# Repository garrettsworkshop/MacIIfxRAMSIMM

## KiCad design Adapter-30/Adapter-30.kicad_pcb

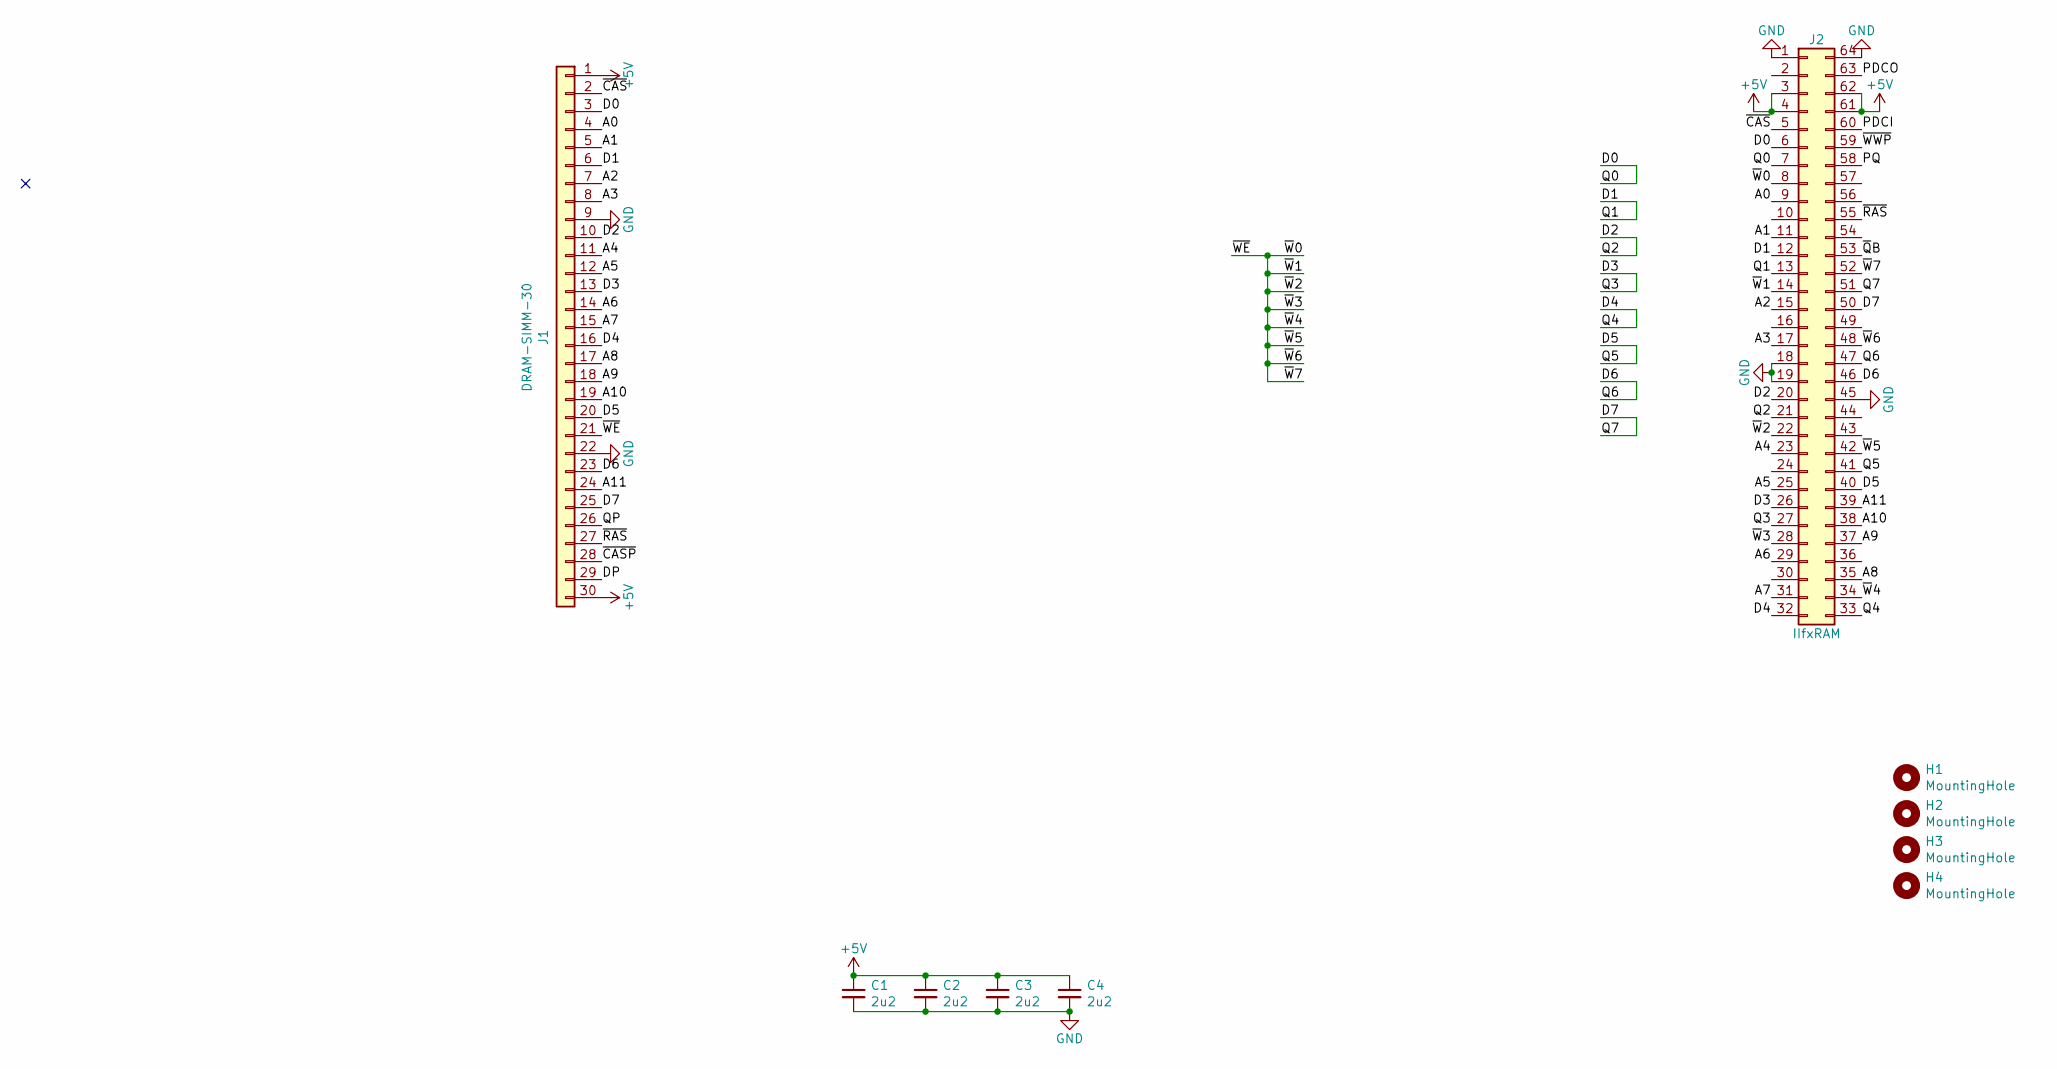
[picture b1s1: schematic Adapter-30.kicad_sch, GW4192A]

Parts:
C1, C2, C3, C4: 2u2; C_0805
H1, H2, H3, H4: MountingHole; PasteHole_1.152mm_NPTH
J1: DRAM-SIMM-30; SIMM-30_Edge
J2: IIfxRAM; SIMM-64_Socket_TH_P1.27mm

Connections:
+5V: C1.1, C2.1, C3.1, C4.1, J1.1, J1.30, J2.3, J2.4, J2.61, J2.62
/A0: J1.4, J2.9
/A1: J1.5, J2.11
/A2: J1.7, J2.15
/A3: J1.8, J2.17
/A4: J1.11, J2.23
/A5: J1.12, J2.25
/A6: J1.14, J2.29
/A7: J1.15, J2.31
/A8: J1.17, J2.35
/A9: J1.18, J2.37
/A10: J1.19, J2.38
/A11: J1.24, J2.39
/D0: J1.3, J2.6, J2.7
/D1: J1.6, J2.12, J2.13
/D2: J1.10, J2.20, J2.21
/D3: J1.13, J2.26, J2.27
/D4: J1.16, J2.32, J2.33
/D5: J1.20, J2.40, J2.41
/D6: J1.23, J2.46, J2.47
/D7: J1.25, J2.50, J2.51
/DP: J1.29
/PDCI: J2.60
/PDCO: J2.63
/PQ: J2.58
/QP: J1.26
/~CASP: J1.28
/~CAS: J1.2, J2.5
/~QB: J2.53
/~RAS: J1.27, J2.55
/~WE: J1.21, J2.8, J2.14, J2.22, J2.28, J2.34, J2.42, J2.48, J2.52
/~WWP: J2.59
GND: C1.2, C2.2, C3.2, C4.2, J1.9, J1.22, J2.1, J2.18, J2.19, J2.45, J2.64

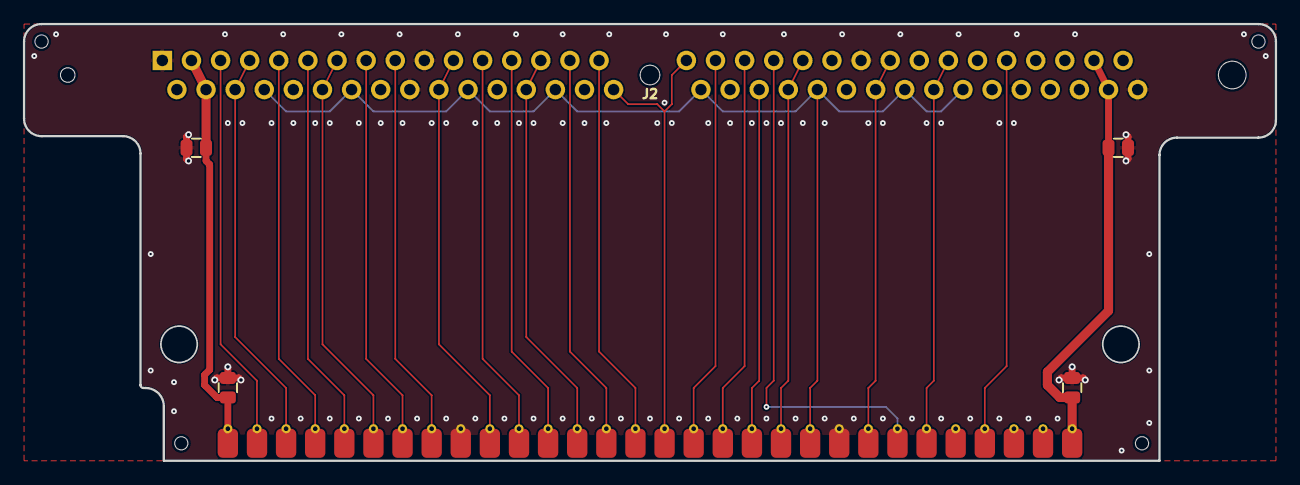
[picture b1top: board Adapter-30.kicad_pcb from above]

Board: 2 copper layers, 109.2 x 38.1 mm, 10 parts (0 on the bottom side), 25 nets.

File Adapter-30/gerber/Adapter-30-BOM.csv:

"Ref","Qnty","Value","Cmp name","Footprint","Description","Vendor","LCSC Part"
"C1, C2, C3, C4, ","4","2u2","C_Small","stdpads:C_0805","Unpolarized capacitor, small symbol","",""
"H1, H2, H3, H4, ","4","MountingHole","MountingHole","stdpads:PasteHole_1.152mm_NPTH","Mounting Hole without connection","",""
"J1, ","1","DRAM-SIMM-30","Conn_01x30","stdpads:SIMM-30_Edge","Generic connector, single row, 01x30, script generated (kicad-library-utils/schlib/autogen/connector/)","",""
"J2, ","1","IIfxRAM","Conn_02x32_Counter_Clockwise","stdpads:SIMM-64_Socket_TH_P1.27mm","Generic connector, double row, 02x32, counter clockwise pin numbering scheme (similar to DIP packge numbering), script generated (kicad-library-utils/schlib/autogen/connector/)","",""

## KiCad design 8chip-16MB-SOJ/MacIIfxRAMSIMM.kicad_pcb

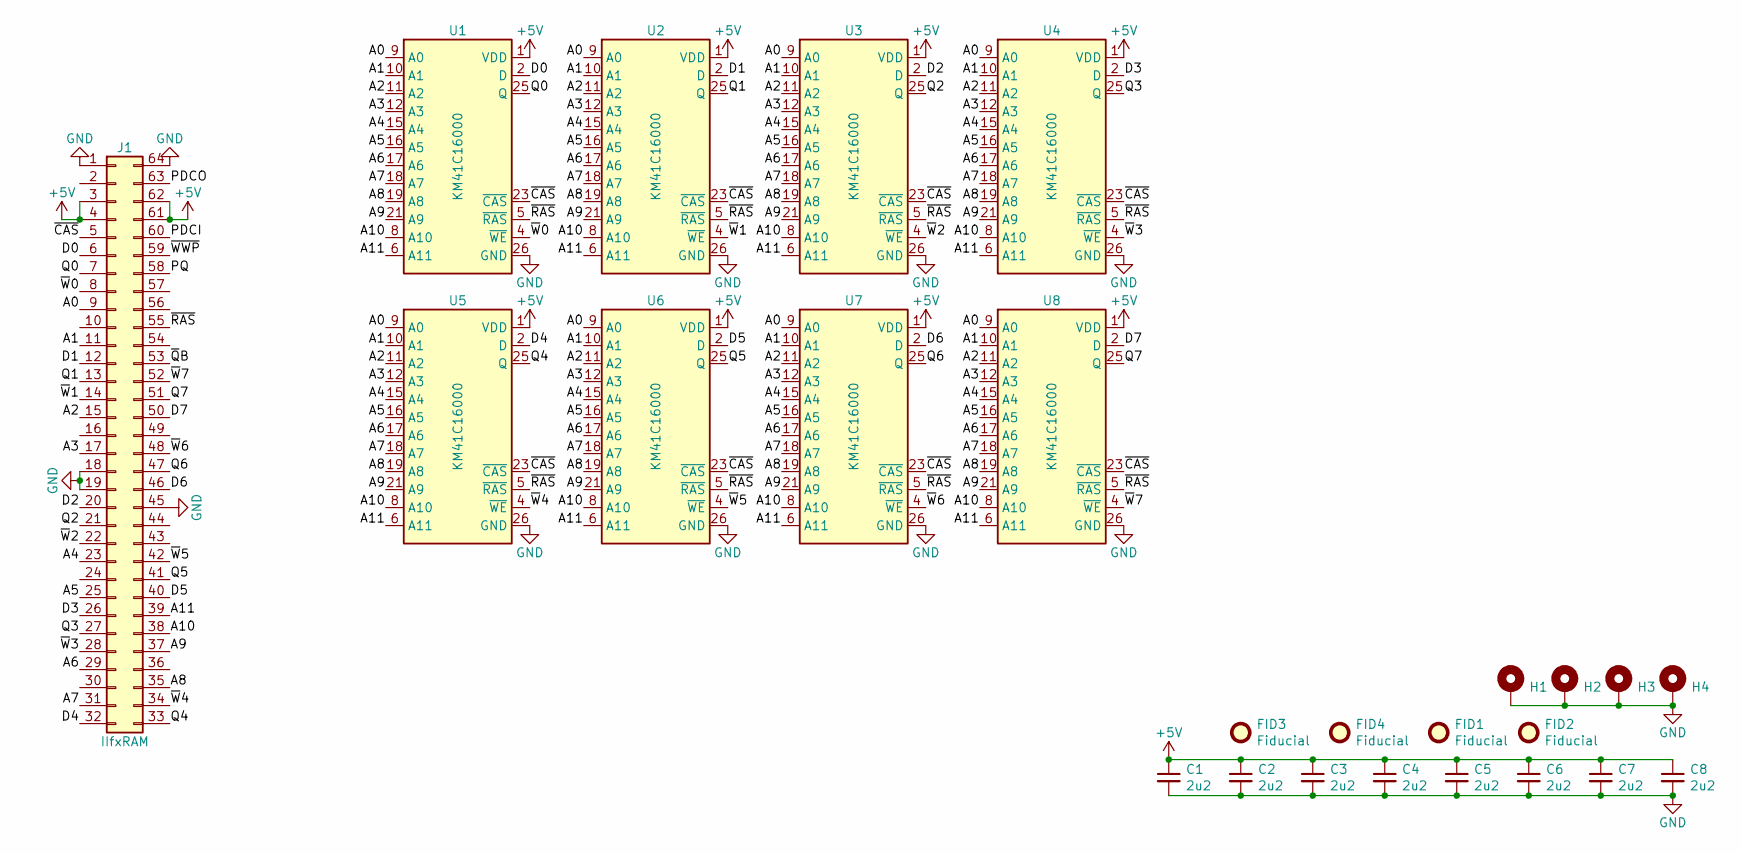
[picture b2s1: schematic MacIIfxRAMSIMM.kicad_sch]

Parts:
C1, C2, C3, C4, C5, C6, C7, C8: 2u2; C_0805
FID1, FID2, FID3, FID4: Fiducial
H1, H2, H3, H4: PasteHole_1.1mm_PTH
J1: IIfxRAM; MacIIROMSIMM_Edge
U1, U2, U3, U4, U5, U6, U7, U8: KM41C16000; SOP-24-26-300mil

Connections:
+5V: C1.1, C2.1, C3.1, C4.1, C5.1, C6.1, C7.1, C8.1, J1.3, J1.4, J1.61, J1.62, U1.1 (VDD), U1.13 (VDD), U2.1 (VDD), U2.13 (VDD), U3.1 (VDD), U3.13 (VDD), U4.1 (VDD), U4.13 (VDD), U5.1 (VDD), U5.13 (VDD), U6.1 (VDD), U6.13 (VDD), U7.1 (VDD), U7.13 (VDD), U8.1 (VDD), U8.13 (VDD); also elsewhere on the board
/A0: J1.9, U1.9 (A0), U2.9 (A0), U3.9 (A0), U4.9 (A0), U5.9 (A0), U6.9 (A0), U7.9 (A0), U8.9 (A0)
/A1: J1.11, U1.10 (A1), U2.10 (A1), U3.10 (A1), U4.10 (A1), U5.10 (A1), U6.10 (A1), U7.10 (A1), U8.10 (A1)
/A2: J1.15, U1.11 (A2), U2.11 (A2), U3.11 (A2), U4.11 (A2), U5.11 (A2), U6.11 (A2), U7.11 (A2), U8.11 (A2)
/A3: J1.17, U1.12 (A3), U2.12 (A3), U3.12 (A3), U4.12 (A3), U5.12 (A3), U6.12 (A3), U7.12 (A3), U8.12 (A3)
/A4: J1.23, U1.15 (A4), U2.15 (A4), U3.15 (A4), U4.15 (A4), U5.15 (A4), U6.15 (A4), U7.15 (A4), U8.15 (A4)
/A5: J1.25, U1.16 (A5), U2.16 (A5), U3.16 (A5), U4.16 (A5), U5.16 (A5), U6.16 (A5), U7.16 (A5), U8.16 (A5)
/A6: J1.29, U1.17 (A6), U2.17 (A6), U3.17 (A6), U4.17 (A6), U5.17 (A6), U6.17 (A6), U7.17 (A6), U8.17 (A6)
/A7: J1.31, U1.18 (A7), U2.18 (A7), U3.18 (A7), U4.18 (A7), U5.18 (A7), U6.18 (A7), U7.18 (A7), U8.18 (A7)
/A8: J1.35, U1.19 (A8), U2.19 (A8), U3.19 (A8), U4.19 (A8), U5.19 (A8), U6.19 (A8), U7.19 (A8), U8.19 (A8)
/A9: J1.37, U1.21 (A9), U2.21 (A9), U3.21 (A9), U4.21 (A9), U5.21 (A9), U6.21 (A9), U7.21 (A9), U8.21 (A9)
/A10: J1.38, U1.8 (A10), U2.8 (A10), U3.8 (A10), U4.8 (A10), U5.8 (A10), U6.8 (A10), U7.8 (A10), U8.8 (A10)
/A11: J1.39, U1.6 (A11), U2.6 (A11), U3.6 (A11), U4.6 (A11), U5.6 (A11), U6.6 (A11), U7.6 (A11), U8.6 (A11)
/D0: J1.6, U1.2 (D)
/D1: J1.12, U2.2 (D)
/D2: J1.20, U3.2 (D)
/D3: J1.26, U4.2 (D)
/D4: J1.32, U5.2 (D)
/D5: J1.40, U6.2 (D)
/D6: J1.46, U7.2 (D)
/D7: J1.50, U8.2 (D)
/PDCI: J1.60
/PDCO: J1.63
/PQ: J1.58
/Q0: J1.7, U1.25 (Q)
/Q1: J1.13, U2.25 (Q)
/Q2: J1.21, U3.25 (Q)
/Q3: J1.27, U4.25 (Q)
/Q4: J1.33, U5.25 (Q)
/Q5: J1.41, U6.25 (Q)
/Q6: J1.47, U7.25 (Q)
/Q7: J1.51, U8.25 (Q)
/~CAS: J1.5, U1.23 (~CAS), U2.23 (~CAS), U3.23 (~CAS), U4.23 (~CAS), U5.23 (~CAS), U6.23 (~CAS), U7.23 (~CAS), U8.23 (~CAS)
/~QB: J1.53
/~RAS: J1.55, U1.5 (~RAS), U2.5 (~RAS), U3.5 (~RAS), U4.5 (~RAS), U5.5 (~RAS), U6.5 (~RAS), U7.5 (~RAS), U8.5 (~RAS)
/~WWP: J1.59
/~W0: J1.8, U1.4 (~WE)
/~W1: J1.14, U2.4 (~WE)
/~W2: J1.22, U3.4 (~WE)
/~W3: J1.28, U4.4 (~WE)
/~W4: J1.34, U5.4 (~WE)
/~W5: J1.42, U6.4 (~WE)
/~W6: J1.48, U7.4 (~WE)
/~W7: J1.52, U8.4 (~WE)
GND: C1.2, C2.2, C3.2, C4.2, C5.2, C6.2, C7.2, C8.2, H1.1, H2.1, H3.1, H4.1, J1.1, J1.18, J1.19, J1.45, J1.64, U1.14 (GND), U1.26 (GND), U2.14 (GND), U2.26 (GND), U3.14 (GND), U3.26 (GND), U4.14 (GND), U4.26 (GND), U5.14 (GND), U5.26 (GND), U6.14 (GND), U6.26 (GND), U7.14 (GND), U7.26 (GND), U8.14 (GND), U8.26 (GND); also elsewhere on the board

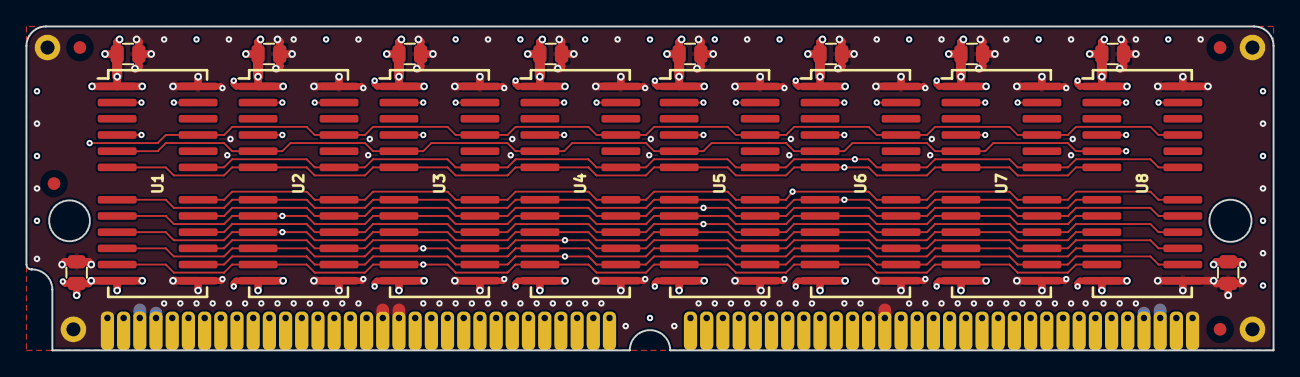
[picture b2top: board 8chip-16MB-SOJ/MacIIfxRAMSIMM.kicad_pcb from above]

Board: 4 copper layers, 97.8 x 25.4 mm, 27 parts (0 on the bottom side), 40 nets.

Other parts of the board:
C8#2, C8#3: 2u2; C_0805

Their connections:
+5V: C8#2.1, C8#3.1; also elsewhere on the board
GND: C8#2.2, C8#3.2; also elsewhere on the board

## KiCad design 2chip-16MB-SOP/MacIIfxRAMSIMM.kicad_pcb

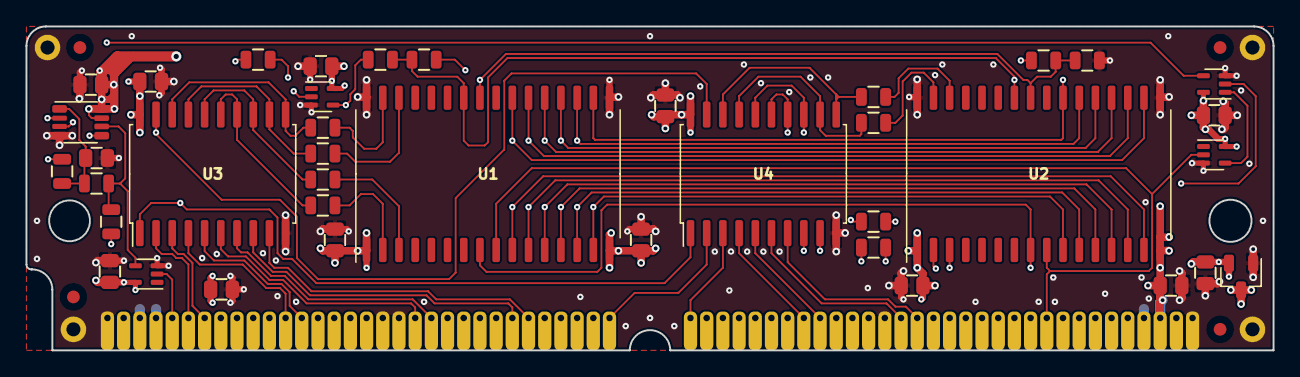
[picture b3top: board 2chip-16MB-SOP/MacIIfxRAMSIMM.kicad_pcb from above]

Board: 4 copper layers, 97.8 x 25.4 mm, 48 parts (0 on the bottom side), 60 nets.

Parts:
C1, C2, C3, C4, C5, C6, C7, C8, C9, C10, C11, C12: 2u2; C_0805
C13: 22p; C_0805
FID1, FID2, FID3, FID4: Fiducial
H1, H2, H3, H4: PasteHole_1.1mm_PTH
J1: IIfxRAM; MacIIROMSIMM_Edge
R1, R2, R3, R4, R5, R6, R7, R8, R9: 100; R_0805
R10: EDO0; R_0805
R11: EDO1; R_0805
R12: FPM; R_0805
R13: CASd; R_0805
R14: CAS; R_0805
R15: RCAS; R_0805
R16: RCASd; R_0805
U1, U2: KM44C16104; SOP-32_400mil
U3, U4: 74AHCT244PW; SOIC-20W_7.5mm
U5, U6, U9: 74LVC1G04GW; SOT-353
U7: 74LVC1G08GW; SOT-353
U8: 74LVC1G74DC; NXP_TSSOP-8_3x3mm_P0.65mm
U10: XC6206PxxxMR; SOT-23

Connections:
+3V3: C8.1, C9.1, C10.1, C11.1, C12.1, U5.5, U6.5, U7.5, U8.7, U8.8, U9.5, U10.2
+5V: C1.1, C2.1, C3.1, C4.1, C5.1, C6.1, C7.1, J1.3, J1.4, J1.61, J1.62, U1.1, U1.16, U2.1, U2.16, U3.20, U4.20, U10.3
/A0: J1.9, U1.10, U2.15
/A1: J1.11, U1.11, U2.14
/A2: J1.15, U1.12, U2.13
/A3: J1.17, U1.13, U2.12
/A4: J1.23, U1.14, U2.11
/A5: J1.25, U1.15, U2.10
/A6: J1.29, U1.23, U2.18
/A7: J1.31, U1.22, U2.19
/A8: J1.35, U1.21, U2.20
/A9: J1.37, U1.20, U2.21
/A10: J1.38, U1.19, U2.22
/A11: J1.39, U1.18, U2.23
/CAS: R1.2, R14.2, U6.4, U8.6
/CASd: C13.1, R1.1, R13.2, U8.1
/D0: J1.6, U3.2
/D1: J1.12, U3.4
/D2: J1.20, U3.6
/D3: J1.26, U3.8
/D4: J1.32, U4.2
/D5: J1.40, U4.4
/D6: J1.46, U4.6
/D7: J1.50, U4.8
/DQ0: R6.1, U3.12, U3.17
/DQ1: R2.1, U3.14, U3.15
/DQ2: R4.1, U3.13, U3.16
/DQ3: R8.1, U3.11, U3.18
/DQ4: R9.1, U4.12, U4.17
/DQ5: R5.1, U4.14, U4.15
/DQ6: R3.1, U4.13, U4.16
/DQ7: R7.1, U4.11, U4.18
/DQr0: R6.2, U1.30
/DQr1: R2.2, U1.2
/DQr2: R4.2, U1.3
/DQr3: R8.2, U1.31
/DQr4: R9.2, U2.31
/DQr5: R5.2, U2.3
/DQr6: R3.2, U2.2
/DQr7: R7.2, U2.30
/Din~OE~: U3.1, U4.1, U8.5
/Dout~OE~: U3.19, U4.19, U8.3
/Q0: J1.7, U3.3
/Q1: J1.13, U3.5
/Q2: J1.21, U3.7
/Q3: J1.27, U3.9
/Q4: J1.33, U4.3
/Q5: J1.41, U4.5
/Q6: J1.47, U4.7
/Q7: J1.51, U4.9
/RAS: U5.4, U7.1
/RD: U7.4, U8.2
/R~CAS~: R15.2, R16.2, U1.26, U2.26
/~CAS~: J1.5, R10.1, R15.1, U6.2
/~CAS~d: R11.1, R16.1, U9.4
/~OE~: R10.2, R11.2, R12.1, U1.25, U2.25
/~RAS~: J1.55, U1.9, U2.9, U5.2
/~WE~: U1.8, U2.8, U7.2
GND: C1.2, C2.2, C3.2, C4.2, C5.2, C6.2, C7.2, C8.2, C9.2, C10.2, C11.2, C12.2, C13.2, H1.1, H2.1, H3.1, H4.1, J1.1, J1.18, J1.19, J1.45, J1.64, R12.2, U1.17, U1.32, U2.17, U2.32, U3.10, U4.10, U5.3, U6.3, U7.3, U8.4, U9.3, U10.1
unnamed: R13.1, R14.1, U9.2

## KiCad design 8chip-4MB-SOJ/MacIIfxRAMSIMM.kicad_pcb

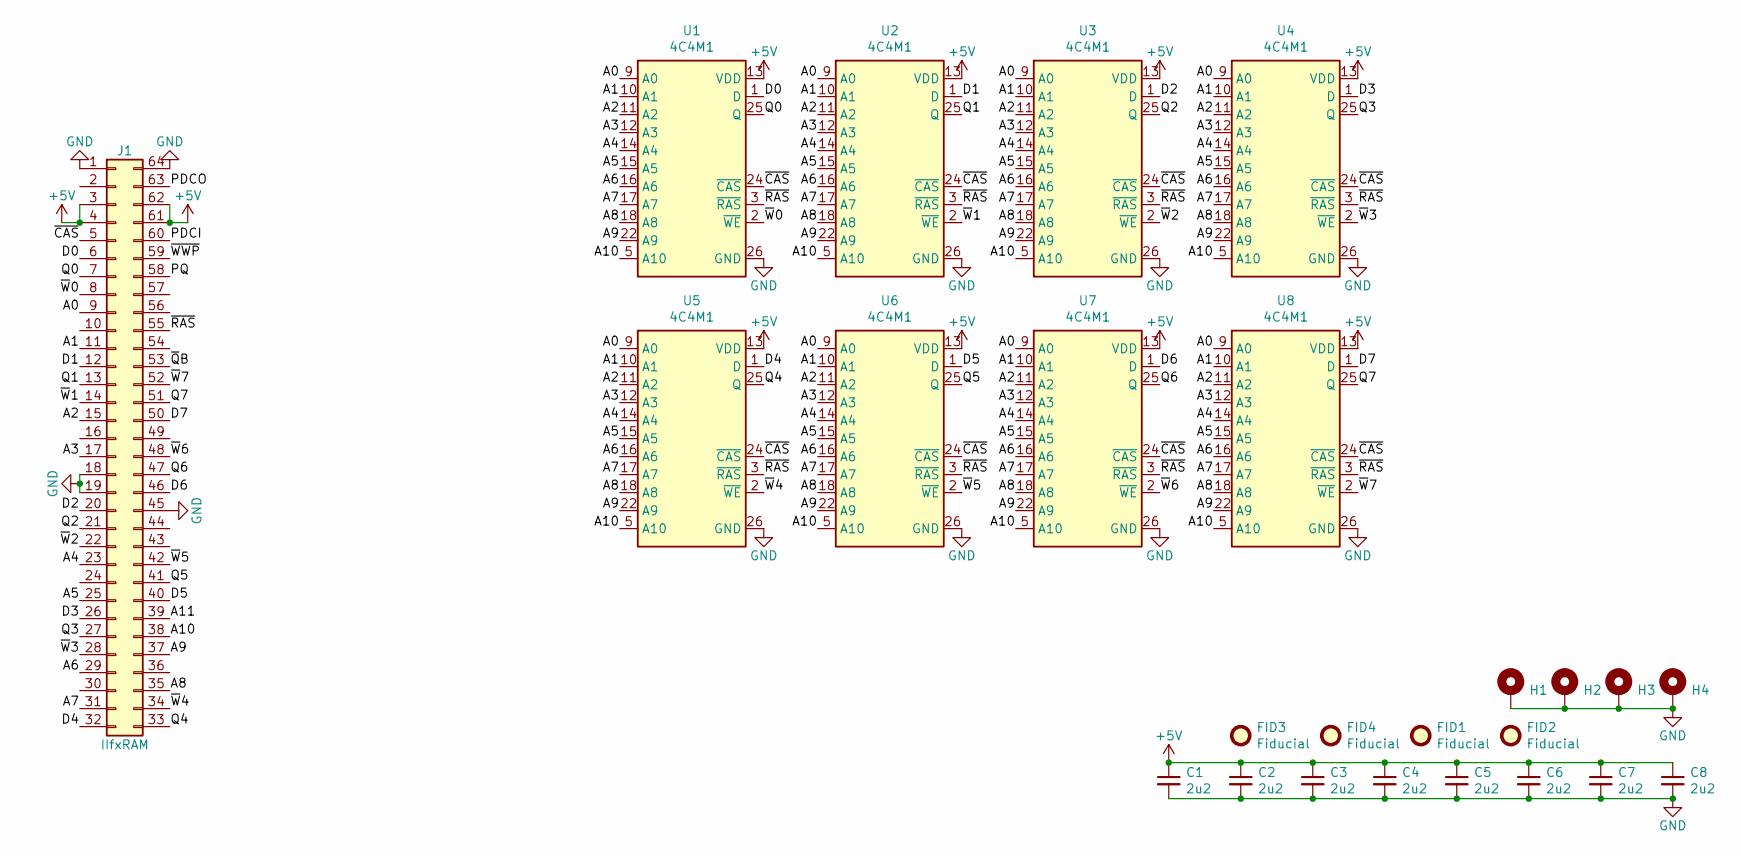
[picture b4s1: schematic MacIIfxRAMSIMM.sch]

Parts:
C1, C2, C3, C4, C5, C6, C7, C8: 2u2; C_0805
FID1, FID2, FID3, FID4: Fiducial
H1, H2, H3, H4: PasteHole_1.1mm_PTH
J1: IIfxRAM; MacIIROMSIMM_Edge
U1, U2, U3, U4, U5, U6, U7, U8: 4C4M1; SOJ-20-26_300mil

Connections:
+5V: C1.1, C2.1, C3.1, C4.1, C5.1, C6.1, C7.1, C8.1, J1.3, J1.4, J1.61, J1.62, U1.13 (VDD), U2.13 (VDD), U3.13 (VDD), U4.13 (VDD), U5.13 (VDD), U6.13 (VDD), U7.13 (VDD), U8.13 (VDD)
/A0: J1.9, U1.9 (A0), U2.9 (A0), U3.9 (A0), U4.9 (A0), U5.9 (A0), U6.9 (A0), U7.9 (A0), U8.9 (A0)
/A1: J1.11, U1.10 (A1), U2.10 (A1), U3.10 (A1), U4.10 (A1), U5.10 (A1), U6.10 (A1), U7.10 (A1), U8.10 (A1)
/A2: J1.15, U1.11 (A2), U2.11 (A2), U3.11 (A2), U4.11 (A2), U5.11 (A2), U6.11 (A2), U7.11 (A2), U8.11 (A2)
/A3: J1.17, U1.12 (A3), U2.12 (A3), U3.12 (A3), U4.12 (A3), U5.12 (A3), U6.12 (A3), U7.12 (A3), U8.12 (A3)
/A4: J1.23, U1.14 (A4), U2.14 (A4), U3.14 (A4), U4.14 (A4), U5.14 (A4), U6.14 (A4), U7.14 (A4), U8.14 (A4)
/A5: J1.25, U1.15 (A5), U2.15 (A5), U3.15 (A5), U4.15 (A5), U5.15 (A5), U6.15 (A5), U7.15 (A5), U8.15 (A5)
/A6: J1.29, U1.16 (A6), U2.16 (A6), U3.16 (A6), U4.16 (A6), U5.16 (A6), U6.16 (A6), U7.16 (A6), U8.16 (A6)
/A7: J1.31, U1.17 (A7), U2.17 (A7), U3.17 (A7), U4.17 (A7), U5.17 (A7), U6.17 (A7), U7.17 (A7), U8.17 (A7)
/A8: J1.35, U1.18 (A8), U2.18 (A8), U3.18 (A8), U4.18 (A8), U5.18 (A8), U6.18 (A8), U7.18 (A8), U8.18 (A8)
/A9: J1.37, U1.22 (A9), U2.22 (A9), U3.22 (A9), U4.22 (A9), U5.22 (A9), U6.22 (A9), U7.22 (A9), U8.22 (A9)
/A10: J1.38, U1.5 (A10), U2.5 (A10), U3.5 (A10), U4.5 (A10), U5.5 (A10), U6.5 (A10), U7.5 (A10), U8.5 (A10)
/A11: J1.39
/D0: J1.6, U1.1 (D)
/D1: J1.12, U2.1 (D)
/D2: J1.20, U3.1 (D)
/D3: J1.26, U4.1 (D)
/D4: J1.32, U5.1 (D)
/D5: J1.40, U6.1 (D)
/D6: J1.46, U7.1 (D)
/D7: J1.50, U8.1 (D)
/PDCI: J1.60
/PDCO: J1.63
/PQ: J1.58
/Q0: J1.7, U1.25 (Q)
/Q1: J1.13, U2.25 (Q)
/Q2: J1.21, U3.25 (Q)
/Q3: J1.27, U4.25 (Q)
/Q4: J1.33, U5.25 (Q)
/Q5: J1.41, U6.25 (Q)
/Q6: J1.47, U7.25 (Q)
/Q7: J1.51, U8.25 (Q)
/~CAS~: J1.5, U1.24 (~CAS~), U2.24 (~CAS~), U3.24 (~CAS~), U4.24 (~CAS~), U5.24 (~CAS~), U6.24 (~CAS~), U7.24 (~CAS~), U8.24 (~CAS~)
/~Q~B: J1.53
/~RAS~: J1.55, U1.3 (~RAS~), U2.3 (~RAS~), U3.3 (~RAS~), U4.3 (~RAS~), U5.3 (~RAS~), U6.3 (~RAS~), U7.3 (~RAS~), U8.3 (~RAS~)
/~WWP~: J1.59
/~W~0: J1.8, U1.2 (~WE~)
/~W~1: J1.14, U2.2 (~WE~)
/~W~2: J1.22, U3.2 (~WE~)
/~W~3: J1.28, U4.2 (~WE~)
/~W~4: J1.34, U5.2 (~WE~)
/~W~5: J1.42, U6.2 (~WE~)
/~W~6: J1.48, U7.2 (~WE~)
/~W~7: J1.52, U8.2 (~WE~)
GND: C1.2, C2.2, C3.2, C4.2, C5.2, C6.2, C7.2, C8.2, H1.1, H2.1, H3.1, H4.1, J1.1, J1.18, J1.19, J1.45, J1.64, U1.26 (GND), U2.26 (GND), U3.26 (GND), U4.26 (GND), U5.26 (GND), U6.26 (GND), U7.26 (GND), U8.26 (GND)

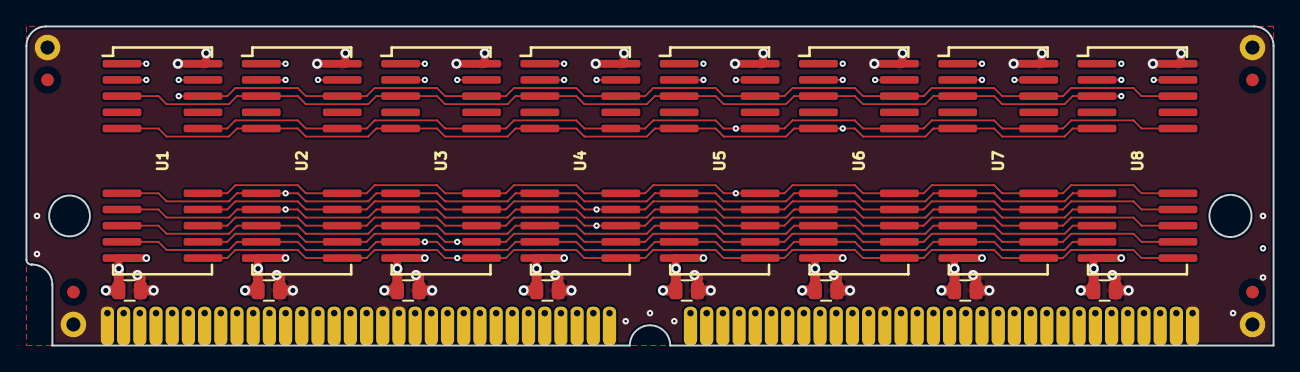
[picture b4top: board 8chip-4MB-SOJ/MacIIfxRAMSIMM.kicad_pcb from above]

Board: 4 copper layers, 97.8 x 25.0 mm, 25 parts (0 on the bottom side), 39 nets.

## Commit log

2021-06-21 Removed 4MB
2021-07-02 Fabbed
2021-10-29 Finished 8-chip layout?
2021-12-06 Add 30-pin SIMM adapter
2021-12-06 8chip SOJ SIMM done?
2022-02-06 Migrate to KiCAD 6
2022-02-06 Switch to KiCAD 6 3dmodels
2022-02-13 Convert schematics to KiCAD 6 too
2022-02-13 Prototype adapter-30
